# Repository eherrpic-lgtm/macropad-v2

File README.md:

A small macropod featuring 12 programmable keys and 2 rotary encoders. Uses a sandwich design to hold down the pcb and 12 mx switches with a top black plate. 
Keys are programmed to optimise coding and make it easier to access things that can be on the harder side of things to do with a normal keyboard, offering quickly accessible shortcuts for key functions

**Materials for 2 macropads** *add 1 microcontroller and 2 rotary encoders and 2 encoder knobs for 1 more*

| Item | Qty | Description | Vendor | Est. Price
| :--- | :---: | :--- | :--- | :---: |
| Custom PCB | 5 | 2-Layer Macropad PCB | JLCPCB | €1.76 |
| Top Plate | 5 | 1.6mm top plate | JLCPCB | €6.49 |
| Microcontroller | 2 | MOUDLE-SEEDUINO-XIAO | [AliExpress](https://de.aliexpress.com/item/1005008200917480.html?spm=a2g0o.cart.0.0.58ee4ae4orNWIU&mp=1&pdp_npi=6%40dis%21CHF%21CHF+13.23%21CHF+9.39%21%21CHF+9.39%21%21%21%402103842a17853297041287864e21a0%2112000058130698584%21ct%21CH%218308305052%21%211%210%21&gatewayAdapt=glo2deu) | €9.39 |
| Switches | 50 | Cherry MX-style mechanical switches | [AliExpress](https://de.aliexpress.com/item/1005012075309061.html?spm=a2g0o.cart.0.0.58ee4ae4orNWIU&mp=1&pdp_npi=6%40dis%21CHF%21CHF+30.41%21CHF+13.99%21%21CHF+13.99%21%21%21%402103842a17853297041287864e21a0%2112000057470352728%21ct%21CH%218308305052%21%211%210%21&gatewayAdapt=glo2deu) | €13.99 |
| Rotary Encoders | 4 | EC11 Encoders | [AliExpress](https://de.aliexpress.com/item/1005007644083514.html?spm=a2g0o.cart.0.0.58ee4ae4orNWIU&mp=1&pdp_npi=6%40dis%21CHF%21CHF+3.12%21CHF+3.12%21%21CHF+3.12%21%21%21%402103842a17853297041287864e21a0%2112000041630839411%21ct%21CH%218308305052%21%211%210%21&gatewayAdapt=glo2deu) | €3.12 |
| Diodes | 100 | 1N4148 Diodes | [AliExpress](https://de.aliexpress.com/item/1005008905065392.html?spm=a2g0o.cart.0.0.58ee4ae4uLiDjA&mp=1&pdp_npi=6%40dis%21CHF%21CHF+1.30%21CHF+1.25%21%21CHF+1.25%21%21%21%4021038a9c17853298451545926e0ece%2112000047140855094%21ct%21CH%218308305052%21%211%210%21&gatewayAdapt=glo2deu) | €1.25 |
| Keycaps & Knobs | 44 | 40x 1u Keycaps + 4x Encoder Knobs | [AliExpress](https://de.aliexpress.com/item/1005007572331245.html?spm=a2g0o.cart.0.0.58ee4ae4uLiDjA&mp=1&pdp_npi=6%40dis%21CHF%21CHF+4.69%21CHF+4.69%21%21CHF+4.69%21%21%21%4021038a9c17853298451545926e0ece%2112000041346783256%21ct%21CH%218308305052%21%212%210%21&gatewayAdapt=glo2deu), [AliExpress](https://de.aliexpress.com/item/1005007969022294.html?spm=a2g0o.cart.0.0.58ee4ae4uLiDjA&mp=1&pdp_npi=6%40dis%21CHF%21CHF+1.93%21CHF+1.93%21%21CHF+1.93%21%21%21%4021038a9c17853298451545926e0ece%2112000043070186687%21ct%21CH%218308305052%21%214%210%21&gatewayAdapt=glo2deu) | €17.1 |
| Case Hardware | 8 | M2 Brass Standoffs + M2 Screws | [AliExpress](https://de.aliexpress.com/item/1005008512900059.html?spm=a2g0o.cart.0.0.58ee4ae4coIEGW&mp=1&pdp_npi=6%40dis%21CHF%21CHF+2.65%21CHF+2.65%21%21CHF+2.65%21%21%21%4021038a9c17853299081077258e0ece%2112000045495593375%21ct%21CH%218308305052%21%211%210%21&gatewayAdapt=glo2deu), [AliExpress](https://www.aliexpress.com/p/shoppingcart/index.html?spm=a2g0o.home.header.1.32097a8bodTR2p), [AliExpress](https://de.aliexpress.com/item/4000314663724.html?spm=a2g0o.cart.0.0.58ee4ae4coIEGW&mp=1&pdp_npi=6%40dis%21CHF%21CHF+1.04%21CHF+0.66%21%21CHF+0.66%21%21%21%4021038a9c17853299081077258e0ece%2110000001297126740%21ct%21CH%218308305052%21%211%210%21&gatewayAdapt=glo2deu) | €6.37 |
| **Total Estimated Cost** | | *(Excluding Shipping)* | | **59.74** |
| **Shipping costs** | | | | |
| AliExpress | | | AliExpress | €8.68 |
| JLCPCB | | | JLCPCB | €10.61 |
 | **Final Estimated Cost** | | | | **€79.03** |

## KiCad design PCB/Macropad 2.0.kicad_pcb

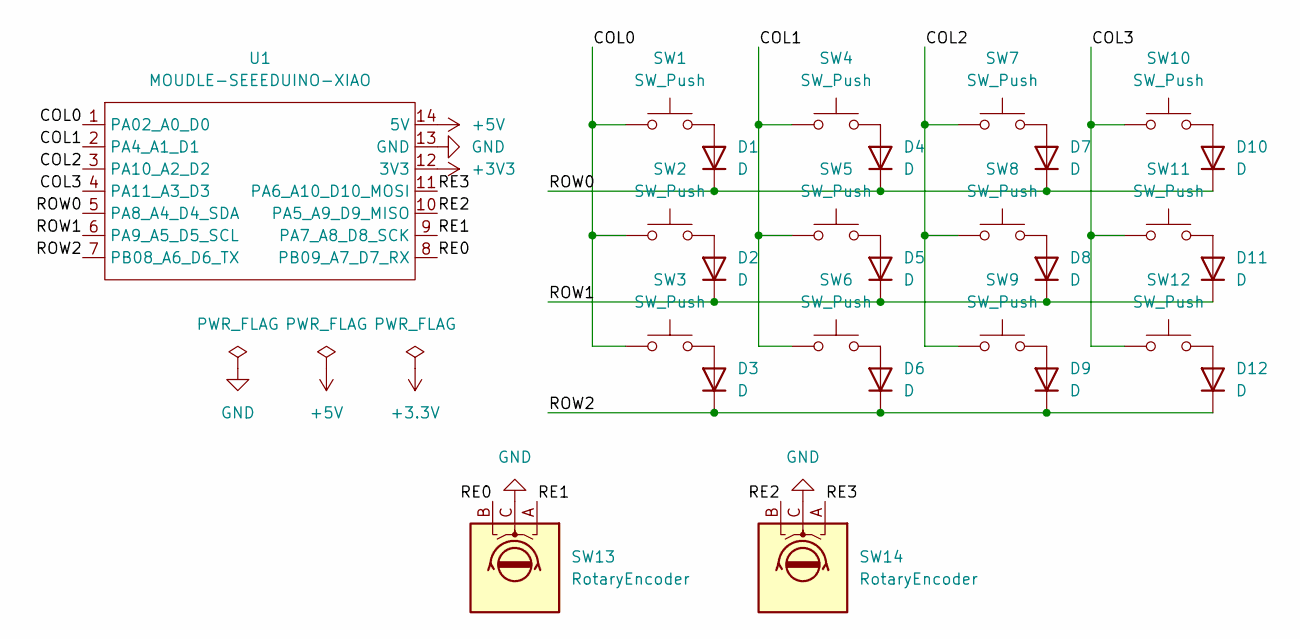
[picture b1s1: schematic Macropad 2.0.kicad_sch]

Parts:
D1, D2, D3, D4, D5, D6, D7, D8, D9, D10, D11, D12: D; D_DO-35_SOD27_P7.62mm_Horizontal
SW1, SW2, SW3, SW4, SW5, SW6, SW7, SW8, SW9, SW10, SW11, SW12: SW_Push; SW_Cherry_MX_1.00u_PCB
SW13, SW14: RotaryEncoder; RotaryEncoder_Alps_EC11E-Switch_Vertical_H20mm
U1: MOUDLE-SEEEDUINO-XIAO; XIAO-Generic-Hybrid-14P-2.54-21X17.8MM

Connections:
+3V3: U1.12 (3V3)
+5V: U1.14 (5V)
/COL0: SW1.1, SW2.1, SW3.1, U1.1 (PA02_A0_D0)
/COL1: SW4.1, SW5.1, SW6.1, U1.2 (PA4_A1_D1)
/COL2: SW7.1, SW8.1, SW9.1, U1.3 (PA10_A2_D2)
/COL3: SW10.1, SW11.1, SW12.1, U1.4 (PA11_A3_D3)
/RE0: SW13.B, U1.8 (PB09_A7_D7_RX)
/RE1: SW13.A, U1.9 (PA7_A8_D8_SCK)
/RE2: SW14.B, U1.10 (PA5_A9_D9_MISO)
/RE3: SW14.A, U1.11 (PA6_A10_D10_MOSI)
/ROW0: D1.1 (K), D4.1 (K), D7.1 (K), D10.1 (K), U1.5 (PA8_A4_D4_SDA)
/ROW1: D2.1 (K), D5.1 (K), D8.1 (K), D11.1 (K), U1.6 (PA9_A5_D5_SCL)
/ROW2: D3.1 (K), D6.1 (K), D9.1 (K), D12.1 (K), U1.7 (PB08_A6_D6_TX)
GND: SW13.C, SW14.C, U1.13 (GND)
unnamed: D1.2 (A), SW1.2
unnamed: D2.2 (A), SW2.2
unnamed: D3.2 (A), SW3.2
unnamed: D4.2 (A), SW4.2
unnamed: D5.2 (A), SW5.2
unnamed: D6.2 (A), SW6.2
unnamed: D7.2 (A), SW7.2
unnamed: D8.2 (A), SW8.2
unnamed: D9.2 (A), SW9.2
unnamed: D10.2 (A), SW10.2
unnamed: D11.2 (A), SW11.2
unnamed: D12.2 (A), SW12.2

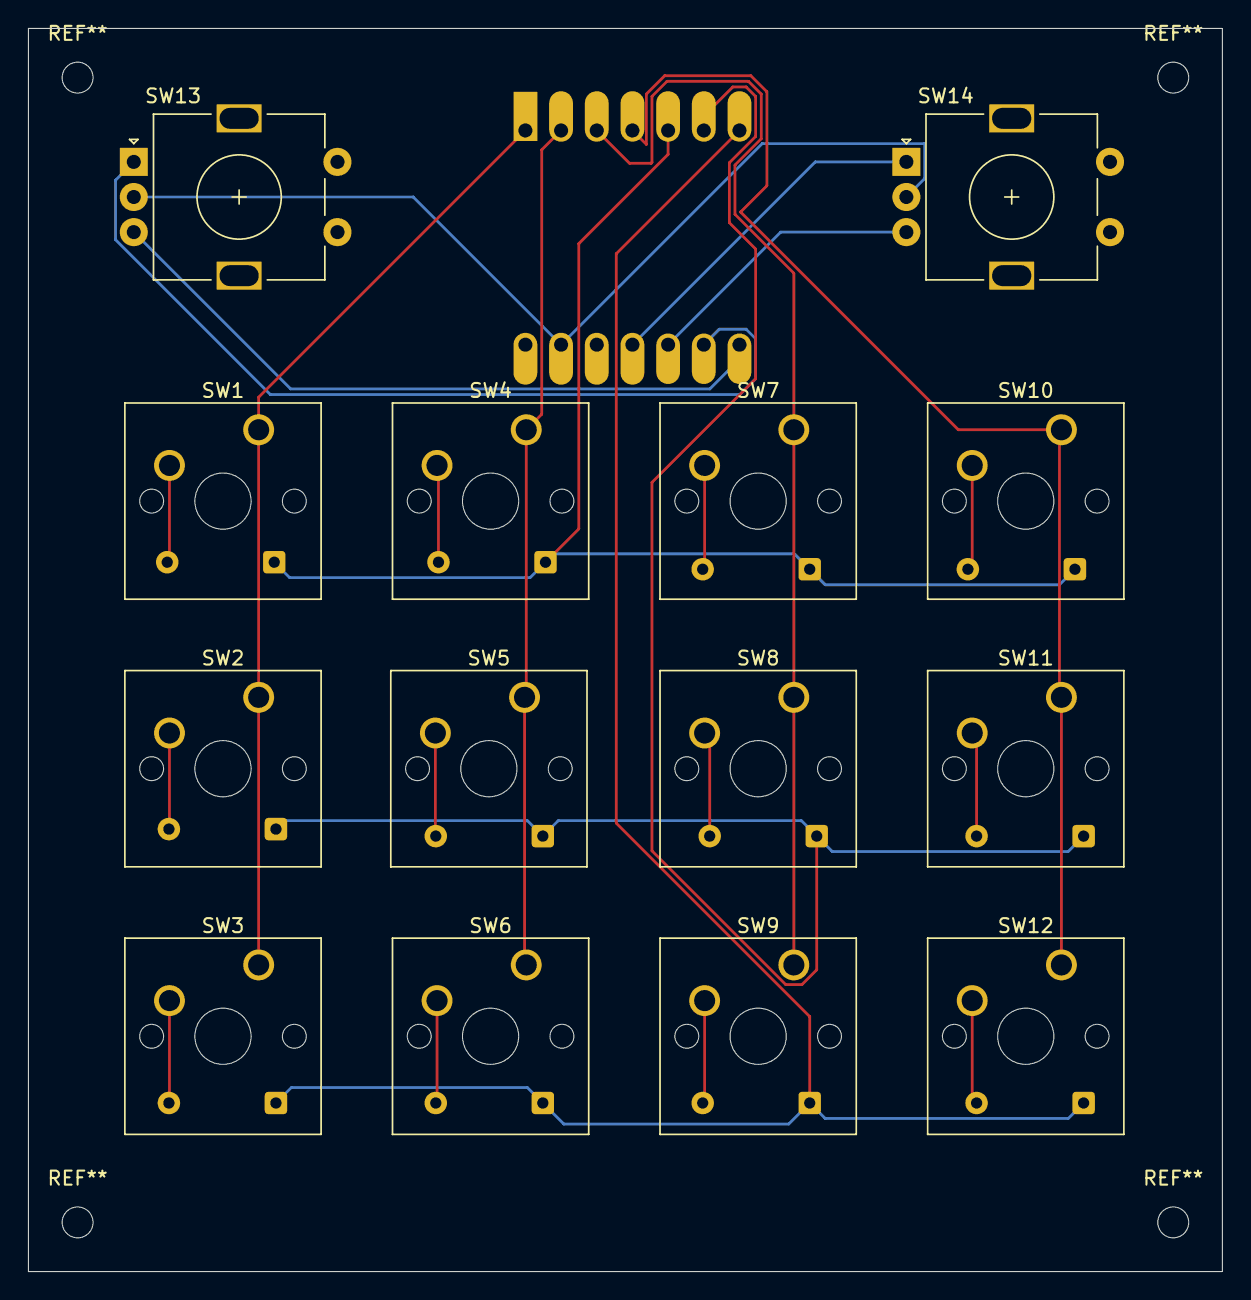
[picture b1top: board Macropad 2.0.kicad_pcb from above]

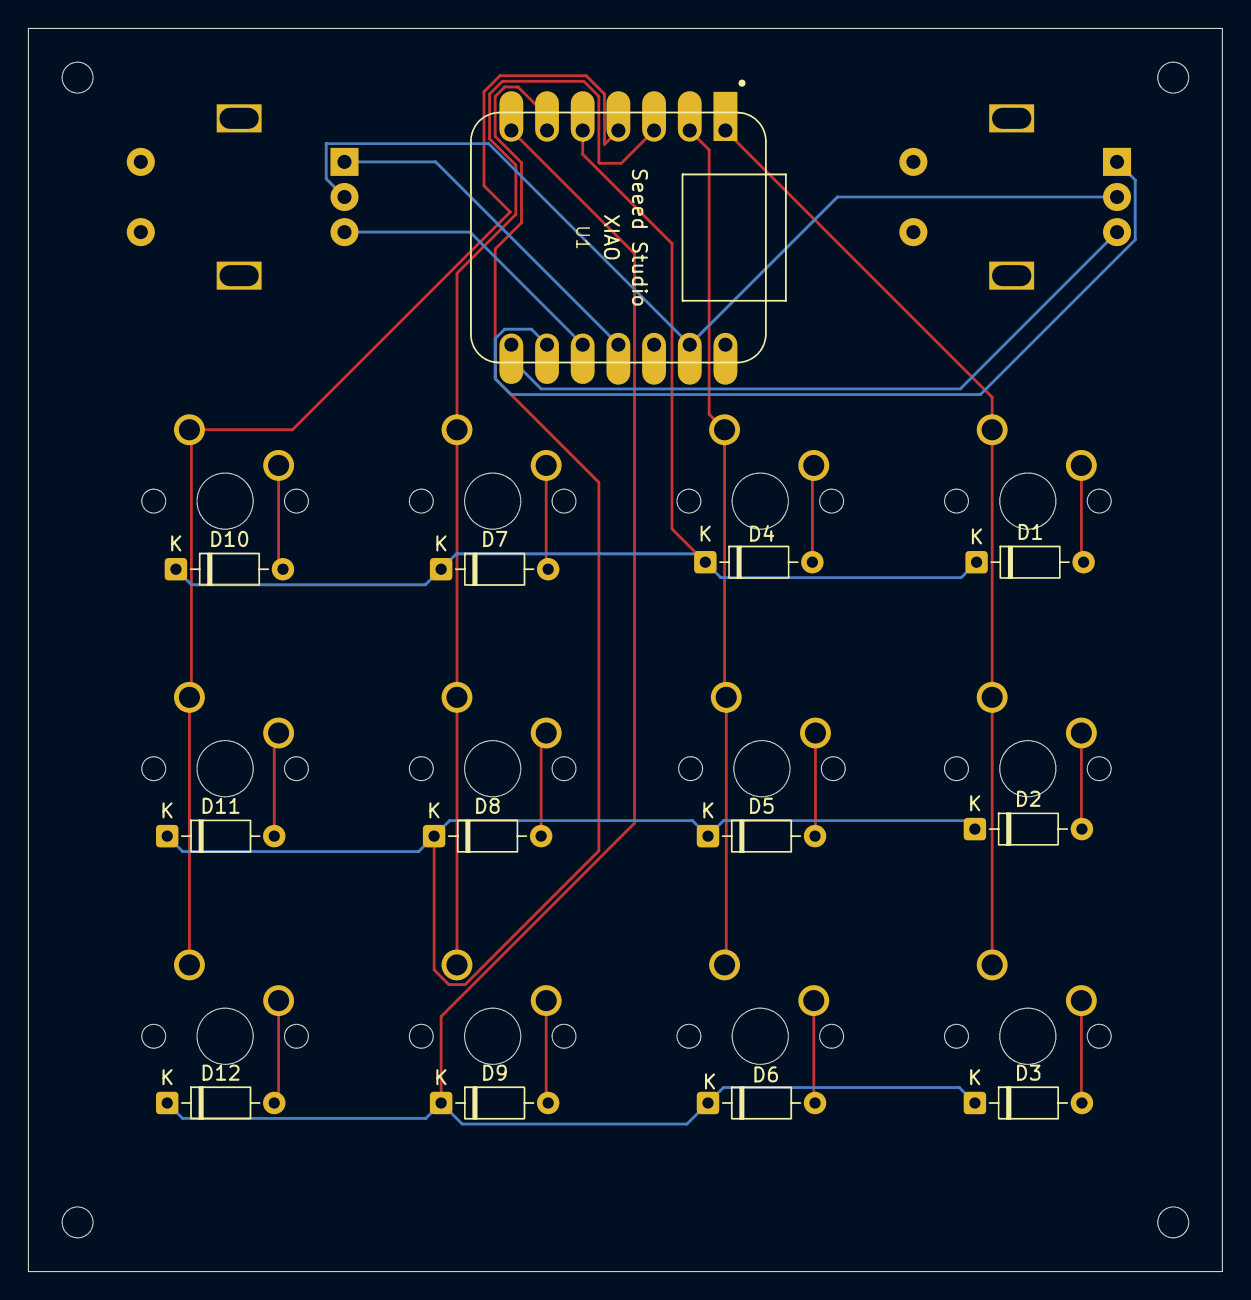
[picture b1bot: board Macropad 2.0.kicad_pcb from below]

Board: 2 copper layers, 85.0 x 88.5 mm, 27 parts (13 on the bottom side), 24 nets.
